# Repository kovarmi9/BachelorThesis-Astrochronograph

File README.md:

# BachelorThesis-Astrochronograph

This repository contains files created for a Bachelor’s Thesis on the topic of ‘Development of a device for receiving and recording coordinated time for astronomical measurement purposes’. It includes the source code of the application and the LaTeX code of the thesis.

**Srtucture of repository:**
<pre>
├── README.md                                    # Documentation
│   ├── src                                      # Source code folder
│   │   ├── Arduino                              # Arduino codes
│   │   │   ├── Components                       # Codes for individual components
│   │   │   │   ├── BLE
│   │   │   │   ├── Bluetooth
│   │   │   │   ├── DCF77_time
│   │   │   │   ├── Display
│   │   │   │   ├── GNSS_time
│   │   │   │   ├── NTP
│   │   │   │   ├── RGB_LED
│   │   │   │   ├── Rotarry_encoder
│   │   │   │   ├── RTC
│   │   │   │   ├── SD
│   │   │   │   ├── Sound
│   │   │   │   └── TS_Reader
│   │   │   ├── Complet
│   │   │   │   ├── Astro-Chronograph_R3
│   │   │   │   └── Astro-Chronograph_R4
│   │   │   └── Test                             # Arduino codes for testing time synchronization
│   │   ├── LaTeX                                # LaTeX source code of the bachelor thesis
│   │   └── R                                    # Processing of testing data
├── Eagle                                        # Circuit schematics and PCB design
└── Text - Text                                  # Text of the Thesis
    ├── Thesis.pdf -                             # Thesis document in PDF format
    └── Presentation.pdf                         # Presentation document in PDF format
</pre>
**Circuit schematics:**

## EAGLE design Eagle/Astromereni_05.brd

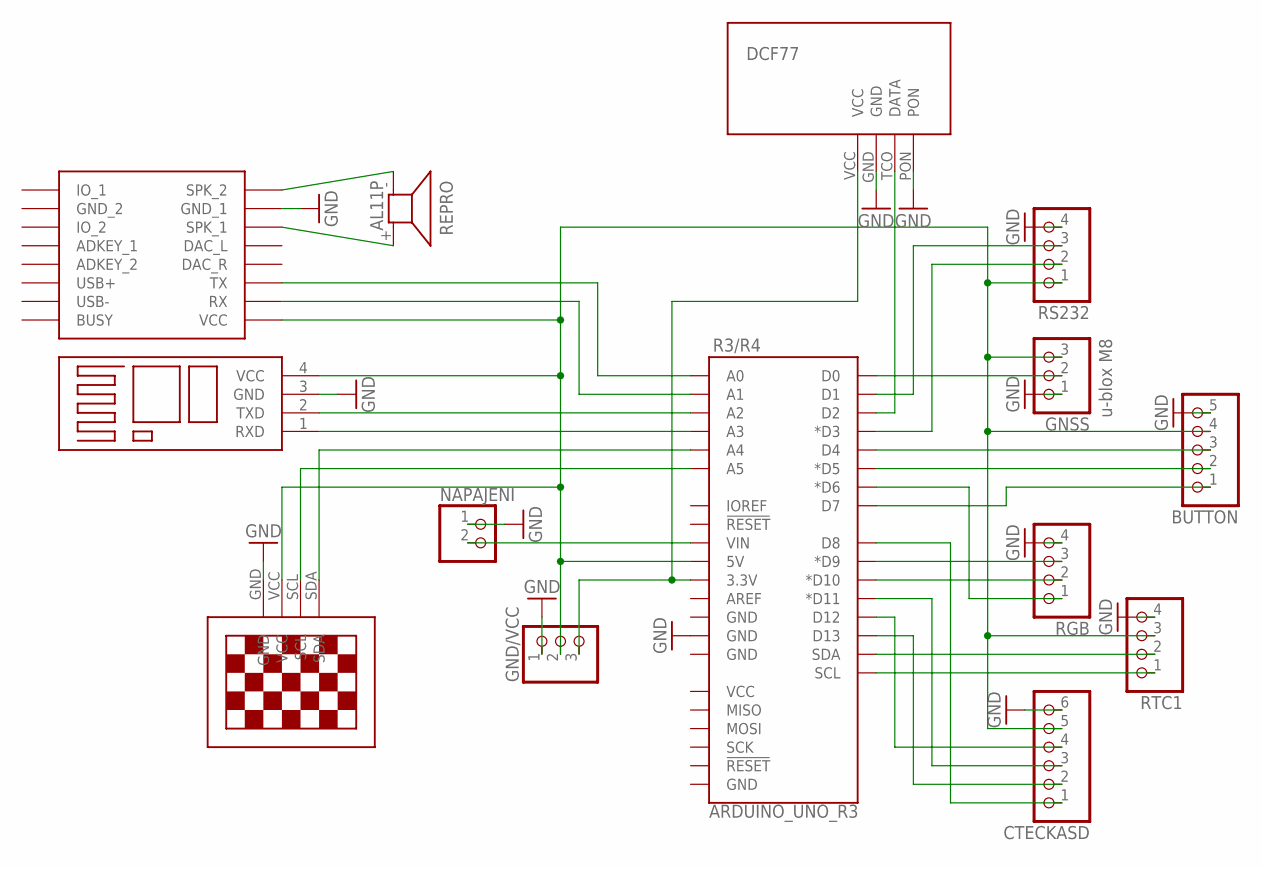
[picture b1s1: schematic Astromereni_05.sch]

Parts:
B4: BLUETOOTH
BUTTON: PINHD-1X5; 1X05
CTECKASD: PINHD-1X6; 1X06
GND/VCC: PINHD-1X3; 1X03
GNSS: PINHD-1X3; 1X03
NAPAJENI: PINHD-1X2; 1X02
R3/R4: ARDUINO_UNO_R3; ARDUINO_R3
REPRO: AL11P
RGB: PINHD-1X4; 1X04
RS232: PINHD-1X4; 1X04
RTC1: PINHD-1X4; 1X04
U$3: DFPLAYER
U$5: 13"OLED13"OLED; 1.3"OLED
U$6: DCF77

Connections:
GND: B4.3 (GND), BUTTON.5, CTECKASD.6, GND/VCC.1, GNSS.1, NAPAJENI.1, R3/R4.GND@3 (GND), RGB.4, RS232.4, RTC1.4, U$3.GND_1, U$5.GND, U$6.GND, U$6.PON
unnamed: CTECKASD.3, R3/R4.D11 (*D11)
unnamed: R3/R4.D6 (*D6), RGB.1
unnamed: BUTTON.1, R3/R4.D7
unnamed: R3/R4.SDA, RTC1.2
unnamed: R3/R4.SCL, RTC1.1
unnamed: GND/VCC.3, R3/R4.3.3V, U$6.VCC
unnamed: CTECKASD.1, R3/R4.D8
unnamed: CTECKASD.4, R3/R4.D12
unnamed: R3/R4.A5, U$5.SCL
unnamed: R3/R4.A4, U$5.SDA
unnamed: GNSS.2, R3/R4.D0
unnamed: REPRO.+ (2), U$3.SPK1 (SPK_1)
unnamed: REPRO.- (1), U$3.SPK2 (SPK_2)
unnamed: B4.2 (TXD), R3/R4.A2
unnamed: B4.1 (RXD), R3/R4.A3
unnamed: R3/R4.D1, RS232.3
unnamed: NAPAJENI.2, R3/R4.VIN
unnamed: R3/R4.D10 (*D10), RGB.2
unnamed: R3/R4.D9 (*D9), RGB.3
unnamed: R3/R4.A1, U$3.RX
unnamed: R3/R4.A0, U$3.TX
unnamed: B4.4 (VCC), BUTTON.4, CTECKASD.5, GND/VCC.2, GNSS.3, R3/R4.5V, RS232.1, RTC1.3, U$3.VCC, U$5.VCC
unnamed: R3/R4.D2, U$6.TCO (DATA)
unnamed: R3/R4.D3 (*D3), RS232.2
unnamed: CTECKASD.2, R3/R4.D13
unnamed: BUTTON.2, R3/R4.D5 (*D5)
unnamed: BUTTON.3, R3/R4.D4

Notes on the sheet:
u-blox M8

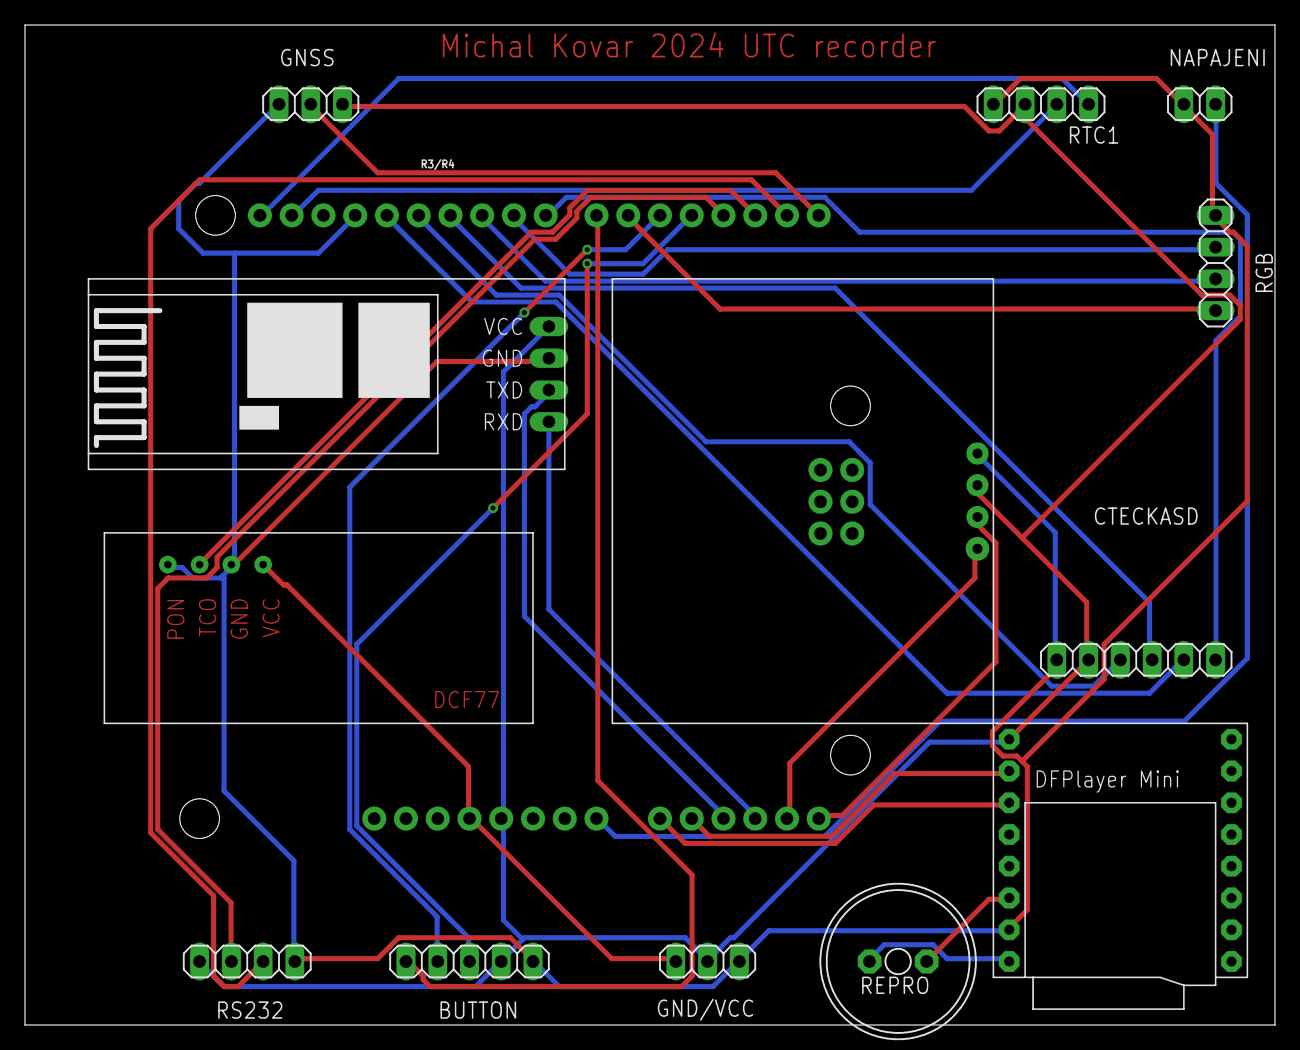
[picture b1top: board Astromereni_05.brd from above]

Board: 2 copper layers, 100.0 x 80.0 mm, 14 parts (0 on the bottom side), 28 nets.

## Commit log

2024-03-07 Přidán kod pro získání času z GNSS přijímače U-blox
2024-03-08 Přidána cesta ke knihovně Arduino
2024-03-08 přidán .gitignore
2024-03-08 Refresh .gitignore
2024-03-21 Přidán kód pro přehrávání zvuku
2024-03-21 Přidány argumenty souboru a hlasitosti do funkce
2024-03-23 Přidán kód pro zápis na microSDkartu
2024-03-24 Přidán kod kombinující několik komponentů
2024-03-24 Upraveno přehrávání zvuku
2024-04-09 Záloha rozdělanách kódů
2024-04-25 přidáno načítání dat z TS a posunut text na displeji
2024-04-29 Přidán kod pro rotační enkoder
2024-05-07 Update README.md
    Doplněna struktura repozitáře do readme
2024-05-07 Přidány kody pro další komponenty
2024-05-07 přidány soubory Eagle
2024-05-08 Přidáno schéma zapojení
2024-05-10 Kod pro UNO R3 okomentářován anglicky
2024-05-13 Přidán gitignore pro te~
2024-05-13 Přidán test chodu dat GNSS
2024-05-13 Update README.md
    Upravena struktura v readme
2024-05-13 Update README.md
    Přidán obrázek schématu zapojení
2024-05-13 Změněn název rezměněny odkazypozitáře
2024-05-17 Přidán kod pro NTP server
2024-05-26 Utřídění souborů
2024-05-26 vytvořeny hlavičkové a implementační soubory
2024-05-26 Aktualizovány soubory v adresáři
2024-05-26 opraveno odsazeni
2024-05-26 Upraveny soubory R
2024-05-26 přidání h a cpp
2024-06-29 přidán latex kod
2024-06-29 přidáno pdf práce
2024-09-14 Přidána prezentace k obhajobě práce
2024-09-14 přejmenovány soubory

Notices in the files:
parts and their libraries:
SparkFun-Boards: Licensing: Creative Commons ShareAlike 4.0 International - https://creativecommons.org/licenses/by-sa/4.0
